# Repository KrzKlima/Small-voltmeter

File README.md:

# Small-voltmeter
The project and all files in this repository are provided under CC BY-NC-SA 4.0 license.

This voltmeter is small (I mean, small), cute, fits on a breadboard and is powered from a 3v3 voltage supply. It even includes a Zener voltage regulator, but for larger supply voltages a dropper resistor is required (0402 resistors have weak power capabilities). The use of bubble display makes reading the voltage easy, despite the minute size of the digits. It uses ATTiny44A and MCP3421 ADC. The board size is 20.5mm by 10.5mm. The device is able to measure its own supply voltage, so no such problems occur as in ICL7107 circuits.

The measurement ranges are the following:
1) -2V to 10V with the resolution of 1mV
2) outside the range 1), within -20 to 100V, with the resolution of 10mV
3) outside the ranges 1) and 2), within -200 to 200V, with the resolution of 100mV
(but you need to observe the safety issues with such high voltages)

Highlights:
- small form factor ~DIP16
- due to the low pin count of the MCU, I2C bus to the external ADC is multiplexed with display outputs - and it still works!
- differential input
- measures ground referenced voltages of both polarities

Two videos showing the operation of the multimeter are linked below.

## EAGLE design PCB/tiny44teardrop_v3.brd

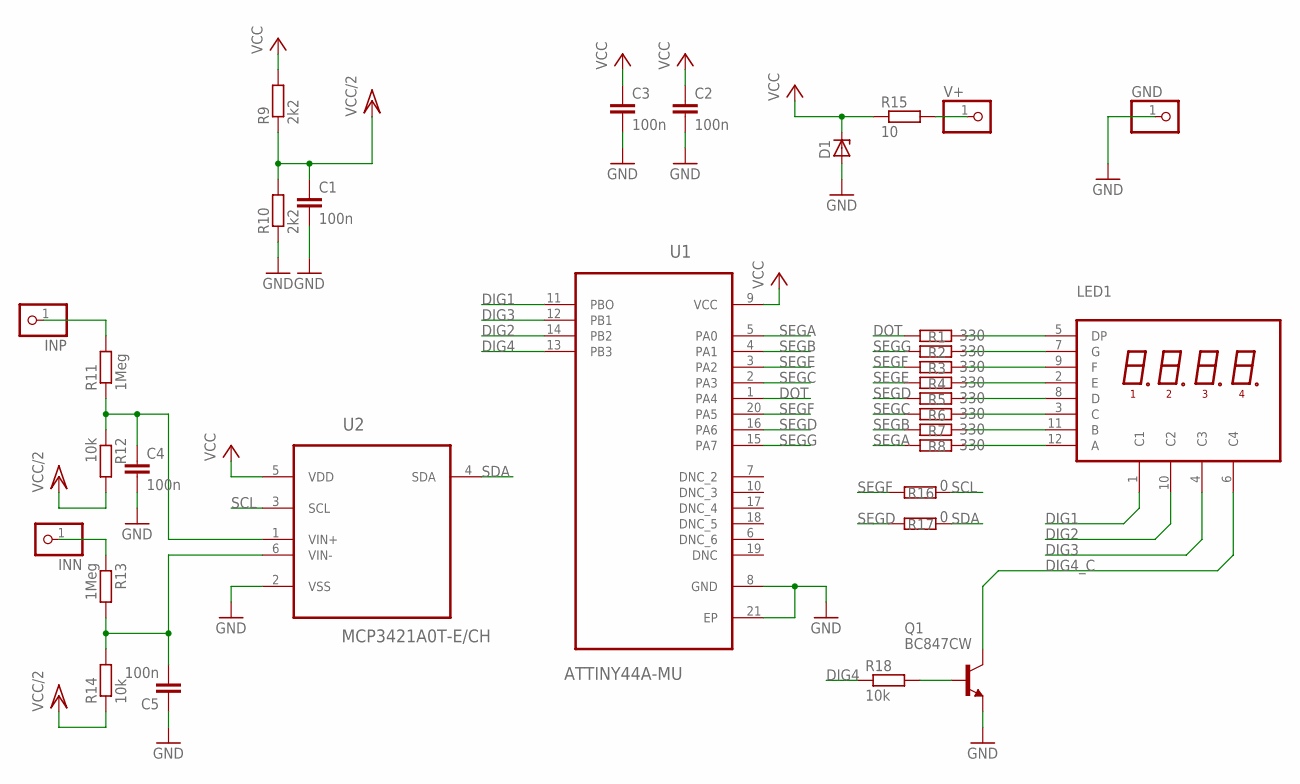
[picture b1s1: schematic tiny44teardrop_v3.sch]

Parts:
C1, C2, C3, C4, C5: 100n; C0603K
D1: BZX84CSMDBZT52C3V3S-7-F; SOD323-R
GND: PINHD-1X1; 1X01
INN: PINHD-1X1; 1X01
INP: PINHD-1X1; 1X01
LED1: 5082-7414
Q1: BC847CW; SOT323-BEC
R1, R2, R3, R4, R5, R6, R7, R8: 330; R0402
R9, R10: 2k2; R0402
R11, R13: 1Meg; R0603
R12, R14, R18: 10k; R0402
R15: 10; R0402
R16, R17: 0; R0402
U1: ATTINY44A-MU; QFN50P400X400X80-21N
U2: MCP3421A0T-E/CH; SOT95P270X145-6N
V+: PINHD-1X1; 1X01

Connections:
DIG1: LED1.1 (C1), U1.11 (PBO)
DIG2: LED1.10 (C2), U1.14 (PB2)
DIG3: LED1.4 (C3), U1.12 (PB1)
DIG4: R18.1, U1.13 (PB3)
DIG4_C: LED1.6 (C4), Q1.C
DOT: R1.1, U1.1 (PA4)
GND: C1.2, C2.2, C3.2, C4.2, C5.1, D1.A, GND.1, Q1.E, R10.1, U1.8 (GND), U1.21 (EP), U2.2 (VSS)
unnamed: LED1.5 (DP), R1.2
unnamed: LED1.7 (G), R2.2
unnamed: R15.2, V+.1
unnamed: LED1.2 (E), R4.2
unnamed: LED1.9 (F), R3.2
unnamed: LED1.3 (C), R6.2
unnamed: LED1.11 (B), R7.2
unnamed: LED1.12 (A), R8.2
unnamed: LED1.8 (D), R5.2
unnamed: INP.1, R11.2
unnamed: Q1.B, R18.2
unnamed: INN.1, R13.1
unnamed: C5.2, R13.2, R14.2, U2.6 (VIN-)
unnamed: C4.1, R11.1, R12.1, U2.1 (VIN+)
SCL: R16.1, U2.3 (SCL)
SDA: R17.1, U2.4 (SDA)
SEGA: R8.1, U1.5 (PA0)
SEGB: R7.1, U1.4 (PA1)
SEGC: R6.1, U1.2 (PA3)
SEGD: R5.1, R17.2, U1.16 (PA6)
SEGE: R4.1, U1.3 (PA2)
SEGF: R3.1, R16.2, U1.20 (PA5)
SEGG: R2.1, U1.15 (PA7)
VCC: C2.1, C3.1, D1.C, R9.2, R15.1, U1.9 (VCC), U2.5 (VDD)
VCC/2: C1.1, R9.1, R10.2, R12.2, R14.1

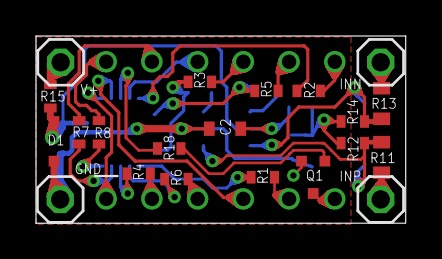
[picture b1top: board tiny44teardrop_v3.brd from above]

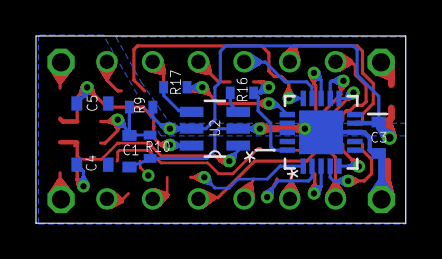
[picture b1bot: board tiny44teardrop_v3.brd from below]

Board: 2 copper layers, 20.5 x 10.4 mm, 32 parts (10 on the bottom side), 32 nets.

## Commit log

2024-08-29 Rename license.txt to LICENSE
2024-08-29 Update LICENSE
2024-08-29 Create description
2024-08-29 Rename tiny44teardrop_v3.zip to gerber_files.zip
